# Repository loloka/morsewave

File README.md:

<div align="center">

# 📡 MorseWave

Русский · 🌐 [English](README.en.md)

**Тёмный минималистичный тренажёр азбуки Морзе**
Буквы по отдельности · Метод Коха · Группы символов · Реальные слова · Позывные · XP и достижения

🌐 **[morse.r9old.ru](https://morse.r9old.ru)** — живая версия

</div>

---

## Что это

MorseWave — веб-тренажёр азбуки Морзе, который проведёт от полного нуля до
приёма на слух реальных позывных и подготовки к сдаче радиолюбительского
экзамена (в «Группах» есть режим экзамена по нормативам «Первой категории»).
Без фреймворков на фронтенде и без Bootstrap: чистый JS (Web Audio API) +
собственная тёмная дизайн-система.

Прогресс (XP, уровень, серия дней, выученные символы) хранится локально
в браузере — регистрация не обязательна, тренироваться можно сразу.
Аккаунт — опциональная надстройка, которая даёт три вещи: место в таблице
лидеров на главной (только по явной кнопке «Опубликовать»), синхронизацию
всего прогресса между устройствами (начал на компьютере — продолжил с
телефона) и восстановление доступа по почте. MySQL под капотом хранит
справочные данные (достижения, банк позывных), анонимную статистику
сообщества, аккаунты и серверные копии прогресса.

Интерфейс двуязычный (русский / английский) — переключатель в шапке рядом
с профилем, подробности в разделе «Как это устроено внутри».

## Возможности

| Раздел | Что внутри |
|---|---|
| 📖 **Буквы** | Три подрежима: отправка ключом (тап/пробел, с живым сайдтоном; три набора — «Латиница + цифры», порядок Коха, кириллица), приём на слух (играет символ → нажми на экранной клавиатуре; отдельный набор «Кириллические символы») и **ритм ключа** (сравнивает реальные длительности точки/тире/пауз с идеалом 1:3:1 — скорость свободно регулируется, идеал пересчитывается под неё; 5 точных повторов подряд оттачивают ритм буквы и дают разовый XP; наборы — «Латиница + цифры» и кириллица, без порядка Коха — он там ни при чём) |
| 👾 **Вторжение** (BETA) | Мини-игра-тауэр-дефенс рядом с «Буквами»: пришельцы летят на базу с буквой на слух, символ надо распознать и нажать на самодельной QWERTY-клавиатуре (или на физической клавиатуре компа) до того, как враг долетит — с базы летит лопата. Скорость врага зависит от сложности кода символа, до 5 одновременных целей по ходу волны из 100 попаданий, победная волна даёт бонус XP от остатка HP базы и скорости реакции |
| 🎯 **Метод Коха** | Символы сразу на целевой скорости; новый символ открывается при точности ≥90%; можно вручную установить любое число открытых символов (в обе стороны) |
| 🔢 **Группы символов** | Приём на слух групп по 2–5 символов: буквы / цифры / микс / только выученные / свои, скорость и интервалы Фарнсворта — слайдерами; режим экзамена по нормативам радиолюбительской категории |
| 📝 **Реальные слова** | Приём частых английских слов и радиообменных фраз (`CQ CQ DE R9OGL K`, `UR RST 599 599`): тренирует узнавание слова единым звуковым образом, а не сборку по буквам. Третий таб в «Группах» |
| 💬 **Сокращения** | Q-коды и радиолюбительские сокращения (CQ, QTH, 73…) на слух с вариантами ответа |
| 📡 **Позывные** | Тренировка на реальных по формату позывных (включая российские форматы), банк расширяется скриптом-генератором |
| 🏆 **Достижения** | Ачивки, условия хранятся в БД (`achievements`) — можно добавлять новые без правки кода |
| 🎯 **Задание дня** | Целевое задание под этап игрока (новичку — «изучи буквы», дальше — «прими на слух», знающему алфавит — группы) + бонус +50 XP раз в день |
| 💡 **Сигнальная лампа** | Визуальный аналог звука — можно тренироваться совсем без звука |
| 🏆 **Таблица лидеров** | Топ-10 на главной по опыту и по серии дней + отдельной строкой настоящее место залогиненного пользователя, если он не попал в десятку; отдельная страница со всей таблицей целиком (`leaderboard.php`), публикация — только по явной кнопке «Опубликовать» |
| 👤 **Аккаунт** | Опционально: синхронизация прогресса между устройствами с индикатором «когда синхронизировано», восстановление пароля по почте, самостоятельное удаление аккаунта |
| 💾 **Бэкап прогресса** | Скачать/загрузить прогресс файлом на странице профиля — аккаунт не нужен. Импорт сливает данные «только вверх», поэтому старый файл поверх нового прогресса безопасен |
| ⚠️ **Сброс прогресса** | Кнопка на странице «Достижения» — полный сброс (localStorage и серверной копии) с подтверждением |
| 🌐 **Русский / English** | Переключатель языка в шапке; письма, юридические страницы и API-ошибки тоже переведены |

## Стек

- **PHP 8+** — без фреймворка, простой роутинг по файлам
- **MySQL / MariaDB** — через PDO
- **Vanilla JS** — Web Audio API для звука, без сборки и npm
- **Кастомный CSS** — дизайн-система в `assets/css/style.css`, без Bootstrap
- **Docker** — для локальной разработки (PHP+Apache, MySQL, phpMyAdmin)

## Запуск и деплой

Коротко — локально через Docker:

```bash
git clone <URL_РЕПО> morse-trainer
cd morse-trainer
docker compose up -d --build
```

Сайт на **http://localhost:8080**, phpMyAdmin на **http://localhost:8081**.

Полные инструкции — запуск без Docker, шпаргалка по командам, деплой на VPS,
миграции базы, настройка почты и **администрирование (кто становится админом
и как передать права)** — в **[DEPLOY.md](DEPLOY.md)**.

## Структура проекта

```
morse-trainer/
├── docker-compose.yml       # локальный запуск: PHP+Apache, MySQL, phpMyAdmin
├── docker/                  # Dockerfile + конфиг Apache (AllowOverride для .htaccess)
├── README.md                 # этот файл — обзор проекта на русском (основной, так видят GitHub-посетители по умолчанию)
├── README.en.md               # обзор проекта на английском
├── DEPLOY.md                  # запуск, деплой, миграции, администрирование
├── CLAUDE.md                 # контекст и правила для Claude Code
├── CHANGELOG.md               # история изменений, v2.49+ (свежие записи сверху)
├── CHANGELOG-archive.md       # история изменений, v2.48 и старше
├── lang/
│   ├── ru.php                # словарь строк интерфейса — русский
│   └── en.php                 # словарь строк интерфейса — английский
├── api/                     # JSON-эндпоинты: achievements, callsigns, stats, register,
│                             #   login, logout, me, sync_progress, refresh_published_stats,
│                             #   leaderboard, verify_email, resend_verification, captcha,
│                             #   admin_users, admin_rename_user, admin_delete_user,
│                             #   admin_set_admin, push_progress, pull_progress,
│                             #   delete_progress, delete_account, request_password_reset,
│                             #   reset_password, update_account, unpublish_stats
├── config/
│   ├── database.example.php # шаблон конфига БД (коммитится)
│   ├── database.php         # реальный конфиг БД с кредами (в .gitignore)
│   ├── mail.example.php      # шаблон конфига почты (коммитится)
│   ├── mail.php               # реальный конфиг почты с ключом (в .gitignore)
│   └── .htaccess               # запрет веб-доступа к папке
├── database/
│   ├── schema.sql            # ЕДИНСТВЕННЫЙ источник истины по схеме БД
│   ├── seed_callsigns.php    # генератор пачки позывных
│   └── .htaccess              # запрет веб-доступа к папке
├── includes/                 # header / footer / nav + auth.php, mailer.php, i18n.php,
│                             #   resend_mailer.php, captcha.php, leaderboard_guard.php
├── storage/sessions/         # файлы PHP-сессий (закрыты .htaccess, в git не хранятся)
├── assets/
│   ├── css/style.css         # дизайн-система
│   └── js/                   # morse-data, daily, audio, progress, signal, input, i18n + страницы
├── index.php                 # главная + задание дня
├── leaderboard.php            # вся таблица лидеров целиком
├── learn.php                 # буквы: отправка / приём на слух / ритм ключа
├── koch.php                  # метод Коха
├── groups.php                # группы символов 2–5 (+ реальные слова, сокращения)
├── callsigns.php              # тренировка позывных
├── achievements.php           # достижения + сброс прогресса
├── account.php                 # профиль (вкладки: аккаунт / звук / отображение / бэкап)
├── terms.php · privacy.php     # пользовательское соглашение и политика конфиденциальности
├── admin.php                    # админка: пользователи, переименование, удаление, выдача прав
└── settings.php                # 301-редирект на account.php (настройки переехали в профиль, v2.24)
```

## За что даётся опыт (XP)

Все начисления округляются до целых. Уровень растёт как `1 + √(XP / 80)`
(т.е. 2-й уровень — 80 XP, 3-й — 320 XP, 5-й — 1280 XP и так далее).

| Режим | Сколько | Условия и защита от фарма |
|---|---|---|
| **Буквы → отправка ключом** | **+25 XP** за символ | Один раз за символ — когда впервые набрана серия из 5 верных повторов подряд. Повторные серии по выученному символу XP не дают. Ставка одинаковая для латиницы и кириллицы — без надбавки за сложность (осознанное упрощение, v2.51.1). |
| **Буквы → приём на слух** | **+1 XP** за верный ответ | Спам верной плиткой в паузе между раундами заблокирован. Ставка одинаковая для латиницы и кириллицы (в v2.51.1 кириллица недолго давала +2, но это путало — одинаково выглядящие латинская и кириллическая «M» получали разный XP; откачено в v2.51.7). |
| **Буквы → ритм ключа** | **+25 XP** разово за букву | Та же анти-фарм схема, что и у отправки ключом: XP не капает за отдельные попытки, а выдаётся один раз, когда набрано 5 точных повторов подряд (буква верная И точность ритма ≥ 80% от идеала 1:3:1). Любая осечка обнуляет серию; повторная тренировка уже отточенной буквы — без XP. |
| **Вторжение** (BETA) | `(База 1 XP) × 2 × (Плотность волны / 3)` (как в Кохе), + бонус `×2` за добивание Босса. Бонус победы волны (10–130 XP). | Награда растет соразмерно плотности волны (количеству пришельцев на экране), используя балансную формулу из Метода Коха/Групп, чтобы предотвратить фарм опыта. Боссы (группы символов) при добивании дают дополнительный опыт, равный их длине ×2. Бонус победы начисляется только за полностью пройденную волну (100 попаданий). |
| **Метод Коха** | `2 × (символов_открыто / 15, но не более 1 и не менее 0.15) × (длина_группы / 3)` XP за каждый верно принятый символ | Чем больше открыто символов и длиннее группы — тем выше ставка (максимум 2 XP/символ при полном наборе). На старте с 2 символами ставка минимальная — фармить лёгкие сессии невыгодно. |
| **Метод Коха — бонус** | **+10/+20/+30 XP** (равен числу групп в сессии) | Только если сессия завершена целиком с точностью ≥ 90 %. Ачивки за метод считаются по честно заработанному уровню (`kochLevelEarned`) — протащить бегунок до конца и получить ачивку нельзя. |
| **Группы символов** | `2 × √(размер_набора / 26, но не более 1 и не менее 0.15) × (длина_группы / 3)` XP за каждый верно принятый символ | Ставка зависит от размера выбранного набора и длины групп. Начисляется сразу за каждую отвеченную группу. |
| **Группы — повтор ошибок** | Опыт **x3** от базового + бонус **5 XP** за безошибочную группу | Генерируются новые случайные группы с замешиванием символов, в которых была ошибка (если перепутал две буквы — в группу попадут обе). Бонус работает как **анти-абуз**: начисляется только если точность в оригинальной сессии была ≥ 60%. Если меньше (умышленный проклик пустых ответов) — XP за ошибки не начисляется (0 XP). |
| **Группы — экзамен** | ставка сессии × верные символы | Только если экзамен доигран до конца — досрочная остановка обнуляет XP экзамена (в общие счётчики группы всё равно идут). |
| **Реальные слова** | **1.2 XP** за символ (слова) / **1.5 XP** (фразы) | Ставка ниже, чем в группах: связный текст предсказуем, недослышанную букву можно восстановить по смыслу. Если слово принято хуже чем на 60 % — XP за него не начисляется вовсе (иначе банк слов фармился бы вслепую). Пробелы во фразах в счёт не идут. |
| **Сокращения (Q-коды)** | **+5 XP** за верный ответ | — |
| **Позывные** | **+20 XP** за верно принятый позывной | Начисляется сразу, не дожидаясь конца сессии. |
| **Задание дня** | **+50 XP** бонусом | Один раз в день. Задание целевое под этап игрока (см. `daily.js`): новичку — «изучи 3 новые буквы», осваивающемуся — «прими 20 символов на слух», знающему алфавит — приём групп. Для группового задания параметры сессии должны совпадать с заданием **и точность быть не ниже 50 %** (прокликать пустые ответы не выйдет, фикс v2.26). |
| **Бонус за скорость (только в задании дня)** | множитель XP `speedXpFactor(wpm)`: ≤12 wpm → ×1.0, выше — +4 %/wpm, потолок ×1.6 (≈27 wpm) | Применяется **только** к групповому заданию дня, где скорость навязана. В обычных сессиях, «Реальных словах» и Кохе не действует — там скорость выбирает сам человек. Смысл: не заставлять новичка гнаться за 24 wpm ради тех же 50 XP, но честно доплачивать за высокий темп. Фарма нет — XP по-прежнему только за верный символ, а быстро принять сложнее. |

### Почему формулы в Кохе и Группах разные

Выглядит как недосмотр, но это осознанное решение (v2.33) — не сводите их
к одной.

В **Группах** набор символов выбирает сам человек, поэтому маленький набор
обязан давать пропорционально меньше XP. Прежний делитель 15 упирался в
потолок слишком рано: свой набор из 15 самых лёгких знаков давал ровно ту
же ставку, что полный алфавит из 36, — это была работающая лазейка.
Делитель 26 (полный латинский алфавит) её закрывает, а корень вместо
линейной пропорции нужен, чтобы честные промежуточные наборы вроде «Цифры»
(10 знаков) не штрафовались слишком жёстко. Числа подобраны так, что оба
основных пресета — «Буквы» (26) и «Буквы + цифры» (36) — дают прежние
2.0 XP/символ: баланс существующих режимов не поехал.

В **Кохе** набор задан уровнем, а не выбором человека. Пофармить маленьким
набором там нельзя в принципе: для этого пришлось бы сидеть на низком
уровне, который и так даёт минимальную ставку. Поэтому формула осталась
старой — ужесточение не закрыло бы ни одной лазейки, зато срезало бы
мотивацию на средних уровнях метода.

Серия дней (🔥 streak) засчитывается только за реальную завершённую
тренировку (сессия Коха/групп/позывных или задание дня) — просто зайти на
сайт недостаточно.

## Как это устроено внутри

- **`assets/js/audio.js`** — `MorseAudio` проигрывает точки/тире через
  осциллятор Web Audio API, поддерживает интервалы Фарнсворта (символы на
  одной скорости, паузы — на другой, более медленной). `onSymbol` колбэк
  отдаёт `durationMs` — используется для точной синхронизации визуализации.
- **`assets/js/input.js`** — `TelegraphKey` превращает удержание клавиши
  (тап по экрану или пробел) в точки/тире по длительности нажатия
  относительно текущего `wpm`, плюс живой сайдтон (реальный звук) во время
  удержания. Пороги: `< 2×unit` → точка, иначе тире; пауза `2.5×unit` —
  граница буквы, ещё `+4×unit` — граница слова.
- **`assets/js/daily.js`** — `DailyChallenge`: единый источник «задания дня»
  для главной и режимов-исполнителей, задание считается из пары
  «дата + этап игрока».
- **`assets/js/signal.js`** — `SignalLine` (осциллограф из точек/тире) и
  `MorseLamp` (визуальная лампа) — сквозные визуальные элементы, синхронно
  отражающие и звук, и ввод на всех страницах тренировки.
- **`assets/js/progress.js`** — весь прогресс пользователя в одном ключе
  `localStorage` (`morsewave_progress_v1`): XP, уровень, серия дней,
  выученные символы, уровень Коха, статистика, разблокированные
  достижения. `Progress.resetAll()` — полный сброс.
- **Синхронизация и её индикатор.** `Progress.pushNow()` шлёт весь
  Progress-объект в `api/push_progress.php` и при ответе `ok: true`
  запоминает момент в отдельном ключе `morsewave_last_sync` + шлёт событие
  `progress:synced`; `account.js` рисует по нему строку «☁ Синхронизировано:
  5 минут назад». Метка ставится **только** при реальном успехе.
- **Бэкап файлом** — `Progress.exportBackup()` / `Progress.importBackup()`.
  Импорт намеренно идёт через тот же `mergeFromServer()`, что и слияние при
  логине: «только вверх» (max по числам, union по множествам). Поэтому
  загрузить старый файл поверх свежего прогресса безопасно.
- **Достижения** определяются в MySQL (`achievements`, поле `condition_type`
  + `condition_value`), а проверка условий против статистики происходит на
  клиенте в `Progress.checkAchievements()` — сопоставление типов см. в
  `progress.js` (`statValue()`).
- **Защита лидерборда** (`includes/leaderboard_guard.php`) — перед публикацией
  в `user_stats` значения обрезаются по правдоподобному потолку (привязан к
  возрасту аккаунта), отсекая грубую накрутку. Реальный прогресс не меняется —
  режется только публичная строка (подробности в CHANGELOG, v2.40).
- **Интернационализация** (`includes/i18n.php`, `lang/ru.php`, `lang/en.php`,
  `assets/js/i18n.js`) — язык выбирается по `?lang=` → cookie `mw_lang` →
  `Accept-Language` браузера → по умолчанию русский. Хелпер `t('ключ')`
  доступен и в PHP-шаблонах, и (как глобальная функция `t()`) в JS через
  `window.MW_I18N`, который `includes/header.php` кладёт в `<head>`.
  Фолбэк при отсутствующем переводе: текущий язык → русский → сам ключ.
  Слоговые мнемоники букв (`MORSE_MNEMONICS` и `CYRILLIC_MNEMONICS` в
  `morse-data.js`) — фонетическая подсказка, завязанная на русское звучание,
  поэтому в английском интерфейсе она осознанно отключена, а не переведена
  дословно.
- **Кириллическая азбука Морзе** (`learn.php`, v2.51) — отдельная таблица
  на 33 кода (`CYRILLIC_CODE`/`CYRILLIC_TO_CHAR` в `morse-data.js`, в обучающем
  наборе 31 буква — `Ъ` и `Ё` исключены из тренировок, чтобы не путать с `Е` и не
  загромождать процесс редкими знаками), намеренно *не* смешанная с латинской
  `MORSE_CODE`/`MORSE_TO_CHAR`: часть кириллических букв совпадает по коду с
  «похожей по звучанию» латинской (так исторически устроена сама азбука), поэтому
  общий реверс-словарь сделал бы декодирование ключом непредсказуемым.
  `TelegraphKey` (`input.js`) принимает таблицу декодирования параметром/через
  `setTable()`, а не жёстко зашитым глобалом. Прогресс по кириллице хранится с
  префиксом `RU_` (`learnedLetters`) — латинская `A` и кириллическая `А` никогда
  не пересекаются, а ачивка «Полный алфавит» считается строго по латинице+цифрам
  (`progress.js`), несмотря на то что кириллические записи лежат в том же массиве.

## История изменений

Актуальная история (v2.49 и новее) — в [CHANGELOG.md](CHANGELOG.md), свежие
записи сверху. Более ранние версии, вплоть до самой первой, —
в [CHANGELOG-archive.md](CHANGELOG-archive.md).

## Известные ограничения / открытые вопросы

- Аккаунты — опциональная надстройка над localStorage (не обязательны для
  тренировки). Клиент остаётся источником истины по XP, поэтому абсолютной
  защиты от накрутки нет; публичный лидерборд прикрыт серверным санитарным
  потолком (`leaderboard_guard.php`, v2.40) — он отсекает грубые значения,
  но это «замок от честных людей», а не пуленепробиваемая защита. Один и тот
  же прогресс из одного браузера технически можно опубликовать от нескольких
  аккаунтов — барьером служит email-подтверждение + мягкое предупреждение
  при повторной публикации.
- Письма шлются через **Resend API** (см. [DEPLOY.md](DEPLOY.md)) — на
  shared-хостинге SMTP оказался ненадёжен (нет DKIM, PTR общего IP не
  указывает на домен, Gmail тихо режет письма).
- Капча на азбуке Морзе (`includes/captcha.php`) — базовая защита от
  примитивных скриптов, не от целенаправленного обхода.
- `TelegraphKey` калибрует точку/тире относительно выбранного `wpm`, а не
  адаптируется к реальному темпу пользователя.
- Кириллица есть только в «Буквах» (отправка + приём на слух) — «Метод Коха»
  и «Группы символов» остаются латинскими. Это осознанно, не недосмотр:
  у Коха фиксированный классический порядок символов, который по
  определению латинский, а Группы/режим экзамена ориентированы на программу
  радиолюбительского экзамена (латиница+цифры) — кириллический набор там
  просто не на что было бы натянуть.

## Roadmap / идеи для развития

Порядок примерно = приоритет (подробности и нюансы — в [CLAUDE.md](CLAUDE.md)):

- [ ] **Свой адаптивный декодер приёма на слух** — подстраивается под
  реальную скорость передачи по таймстемпам, а не под выбранный wpm
- [ ] **Адаптивная калибровка ключа** под реальный темп пользователя
- [ ] _(дальний прицел)_ Нативное Android-приложение (не PWA)
- [ ] _(исследование)_ Подключение реального телеграфного ключа (адаптер на
  Arduino / Web Serial / микрофонный вход)

Уже сделано: восстановление пароля по почте, экспорт/импорт прогресса файлом,
целевые задания дня, самостоятельное удаление аккаунта, защита лидерборда,
двуязычный интерфейс (русский/английский), кириллическая азбука Морзе в
«Буквах» (v2.51), полная таблица лидеров + своё место на главной (v2.52),
оценка ритма ключа в «Буквах» (v2.53), мини-игра «Вторжение» — тауэр-дефенс
на азбуку Морзе (v2.54, статус BETA), достижения за волны вторжения и за
отточенный ритм ключа (v2.55–v2.56).

## Смежный проект

Освоил приём отдельных знаков и позывных — дальше по маршруту (см. «Путь
новичка» на главной) идёт **[Morse Walker](https://morse.r9o.ru)**:
симулятор радиосвязи с pile-up, режимы контестов и POTA, генератор
российских позывных. Это отдельный проект, не часть MorseWave — исходный
автор [W6NYC](https://github.com/sc0tfree/morsewalker), доработка и
русификация — тоже R9OGL: [github.com/loloka/morsewalker](https://github.com/loloka/morsewalker).

## Лицензия

MIT — делай с этим что хочешь, см. [LICENSE](LICENSE).

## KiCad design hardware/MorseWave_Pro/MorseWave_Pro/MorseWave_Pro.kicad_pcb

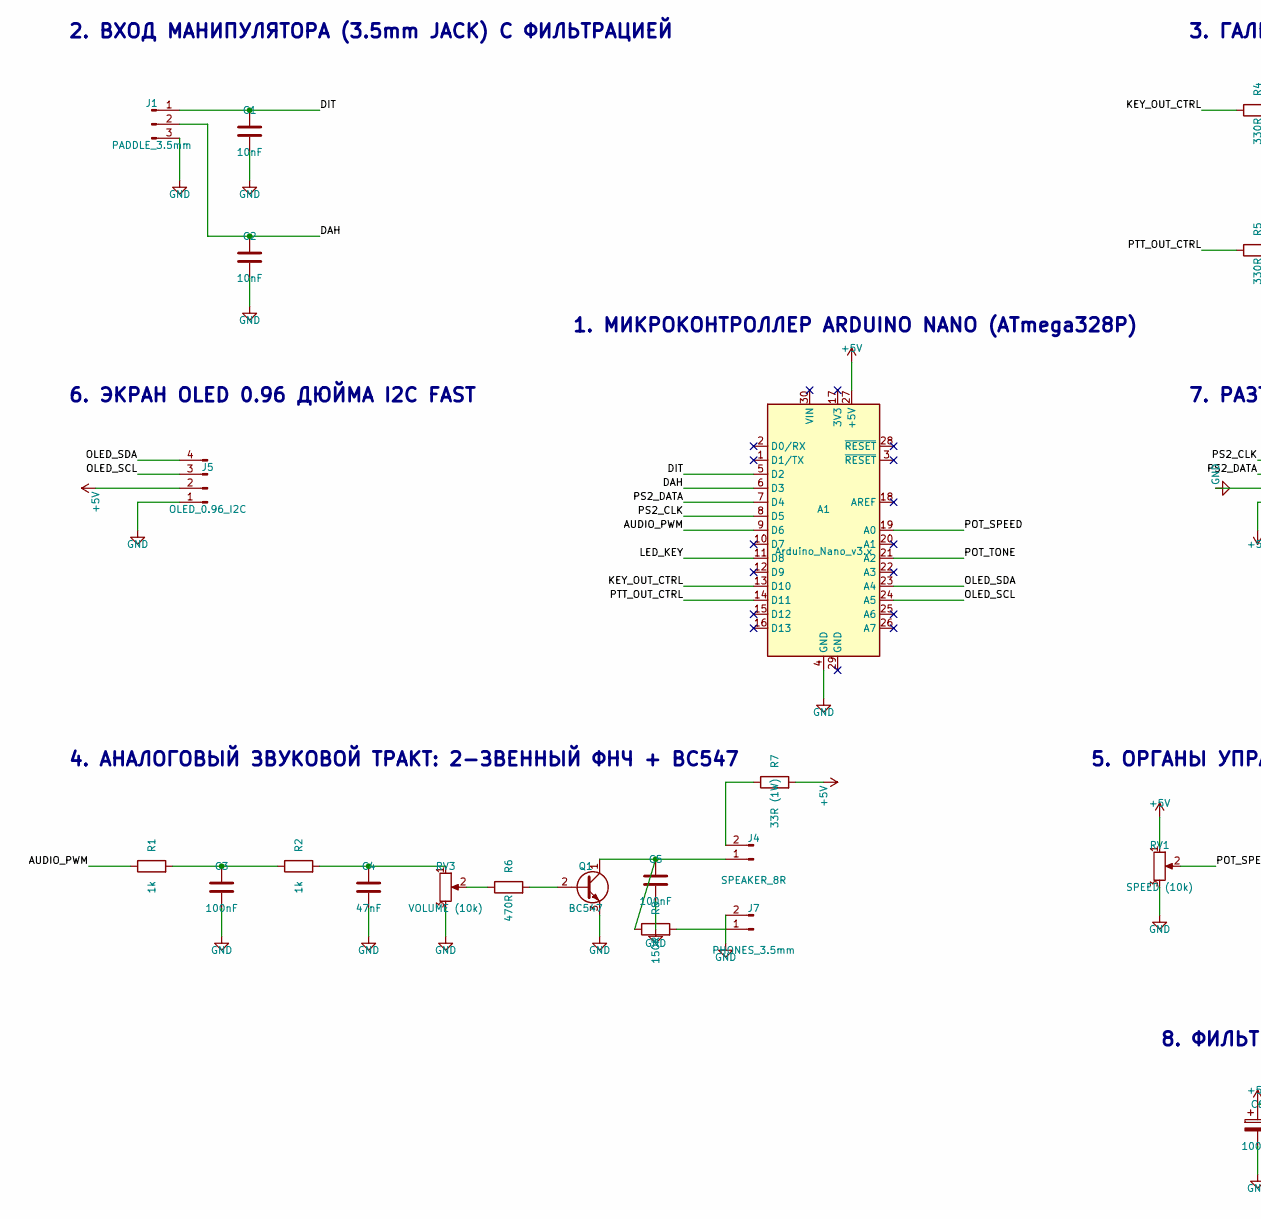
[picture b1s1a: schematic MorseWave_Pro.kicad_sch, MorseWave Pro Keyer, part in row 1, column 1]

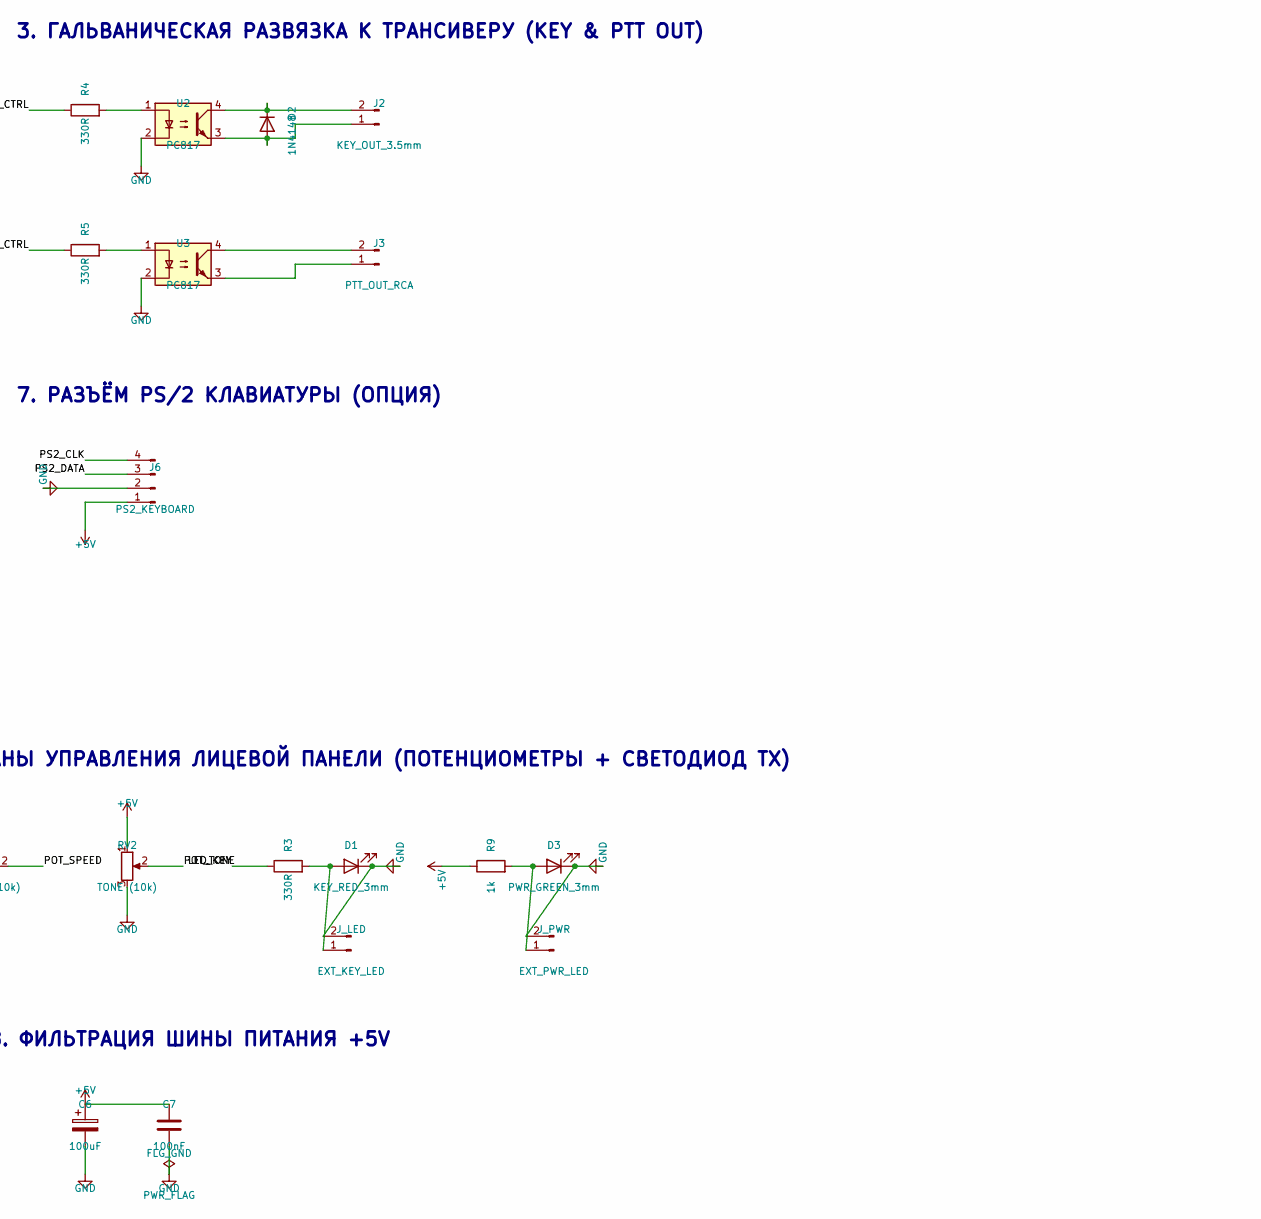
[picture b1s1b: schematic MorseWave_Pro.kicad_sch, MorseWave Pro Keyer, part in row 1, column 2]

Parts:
A1: Arduino_Nano_v3.x; Arduino_Nano
C1, C2: 10nF; C_Disc_D5.0mm_W2.5mm_P5.00mm
C3, C5, C7: 100nF; C_Disc_D5.0mm_W2.5mm_P5.00mm
C4: 47nF; C_Disc_D5.0mm_W2.5mm_P5.00mm
C6: 100uF; CP_Radial_D6.3mm_P2.50mm
D1: KEY_RED_3mm; LED_D3.0mm
D2: 1N4148; D_DO-35_SOD27_P7.62mm_Horizontal
D3: PWR_GREEN_3mm; LED_D3.0mm
FLG_GND: PWR_FLAG
J1: PADDLE_3.5mm; PinHeader_1x03_P2.54mm_Vertical
J2: KEY_OUT_3.5mm; PinHeader_1x02_P2.54mm_Vertical
J3: PTT_OUT_RCA; PinHeader_1x02_P2.54mm_Vertical
J4: SPEAKER_8R; PinHeader_1x02_P2.54mm_Vertical
J5: OLED_0.96_I2C; PinSocket_1x04_P2.54mm_Vertical
J6: PS2_KEYBOARD; PinHeader_1x04_P2.54mm_Vertical
J7: PHONES_3.5mm; PinHeader_1x02_P2.54mm_Vertical
J_LED: EXT_KEY_LED; PinHeader_1x02_P2.54mm_Vertical
J_PWR: EXT_PWR_LED; PinHeader_1x02_P2.54mm_Vertical
Q1: BC547; TO-92_Inline
R1, R2, R9: 1k; R_Axial_DIN0207_L6.3mm_D2.5mm_P7.62mm_Horizontal
R3, R4, R5: 330R; R_Axial_DIN0207_L6.3mm_D2.5mm_P7.62mm_Horizontal
R6: 470R; R_Axial_DIN0207_L6.3mm_D2.5mm_P7.62mm_Horizontal
R7: 33R (1W); R_Axial_DIN0411_L9.9mm_D3.6mm_P12.70mm_Horizontal
R8: 150R; R_Axial_DIN0207_L6.3mm_D2.5mm_P7.62mm_Horizontal
RV1: SPEED (10k); PinHeader_1x03_P2.54mm_Vertical
RV2: TONE (10k); PinHeader_1x03_P2.54mm_Vertical
RV3: VOLUME (10k); PinHeader_1x03_P2.54mm_Vertical
U2, U3: PC817; DIP-4_W7.62mm

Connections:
+5V: A1.27 (+5V), C6.1, C7.1, J5.2, J6.1, R7.2, R9.1, RV1.1, RV2.1
/AUDIO_PWM: A1.9 (D6), R1.1
/DAH: A1.6 (D3), C2.1, J1.2
/DIT: A1.5 (D2), C1.1, J1.1
/KEY_OUT_CTRL: A1.13 (D10), R4.1
/LED_KEY: A1.11 (D8), R3.1
/OLED_SCL: A1.24 (A5), J5.3
/OLED_SDA: A1.23 (A4), J5.4
/POT_SPEED: A1.19 (A0), RV1.2
/POT_TONE: A1.21 (A2), RV2.2
/PS2_CLK: A1.8 (D5), J6.4
/PS2_DATA: A1.7 (D4), J6.3
/PTT_OUT_CTRL: A1.14 (D11), R5.1
GND: A1.4 (GND), C1.2, C2.2, C3.2, C4.2, C5.2, C6.2, C7.2, D1.1 (K), D3.1 (K), FLG_GND.1, J1.3, J5.1, J6.2, J7.2, J_LED.2, J_PWR.2, Q1.3 (E), RV1.3, RV2.3, RV3.3, U2.2, U3.2
unnamed: C3.1, R1.2, R2.1
unnamed: C4.1, R2.2, RV3.1
unnamed: D1.2 (A), J_LED.1, R3.2
unnamed: D2.2 (A), J2.1, U2.3
unnamed: D2.1 (K), J2.2, U2.4
unnamed: D3.2 (A), J_PWR.1, R9.2
unnamed: J3.1, U3.3
unnamed: J3.2, U3.4
unnamed: C5.1, J4.1, Q1.1 (C), R8.1
unnamed: J4.2, R7.1
unnamed: J7.1, R8.2
unnamed: Q1.2 (B), R6.2
unnamed: R4.2, U2.1
unnamed: R5.2, U3.1
unnamed: R6.1, RV3.2

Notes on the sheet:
1. МИКРОКОНТРОЛЛЕР ARDUINO NANO (ATmega328P)
2. ВХОД МАНИПУЛЯТОРА (3.5mm JACK) С ФИЛЬТРАЦИЕЙ
3. ГАЛЬВАНИЧЕСКАЯ РАЗВЯЗКА К ТРАНСИВЕРУ (KEY & PTT OUT)
4. АНАЛОГОВЫЙ ЗВУКОВОЙ ТРАКТ: 2-ЗВЕННЫЙ ФНЧ + BC547
5. ОРГАНЫ УПРАВЛЕНИЯ ЛИЦЕВОЙ ПАНЕЛИ (ПОТЕНЦИОМЕТРЫ + СВЕТОДИОД TX)
6. ЭКРАН OLED 0.96 ДЮЙМА I2C FAST
7. РАЗЪЁМ PS/2 КЛАВИАТУРЫ (ОПЦИЯ)
8. ФИЛЬТРАЦИЯ ШИНЫ ПИТАНИЯ +5V

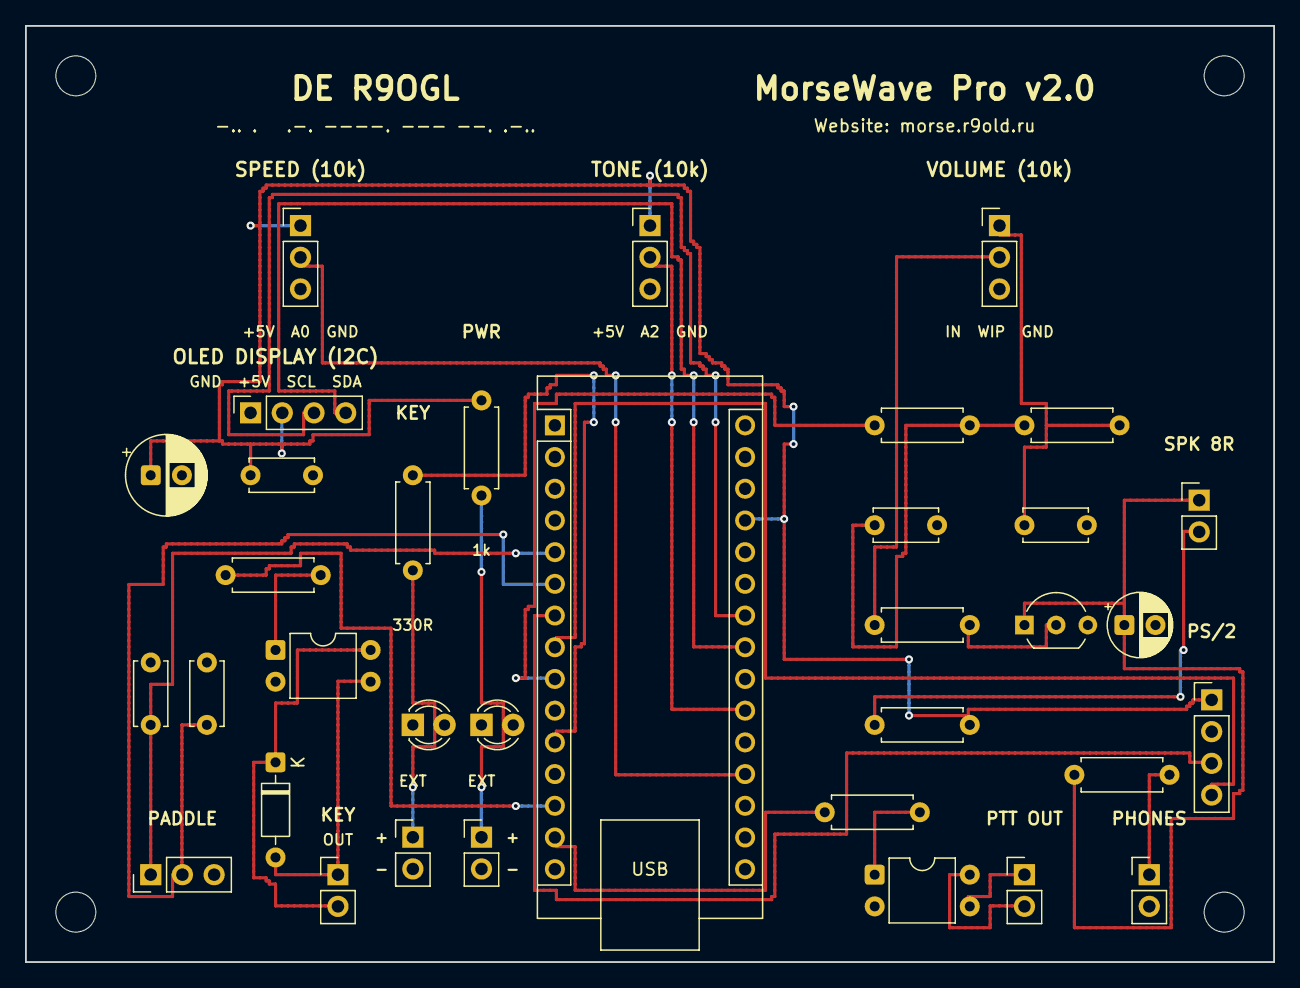
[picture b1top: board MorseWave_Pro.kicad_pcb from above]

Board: 2 copper layers, 100.0 x 75.0 mm, 39 parts (0 on the bottom side), 29 nets.

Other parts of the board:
H1, H2, H3, H4: MountingHole_M3; MountingHole_3.2mm_M3

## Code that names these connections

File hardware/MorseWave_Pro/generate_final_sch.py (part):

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s.no_connect(*s.pin_pos("A1", 2))
s.no_connect(*s.pin_pos("A1", 1))

# D2 (DIT) - Nano pin 5
p_d2 = s.pin_pos("A1", 5)
s.wr(p_d2[0], p_d2[1], p_d2[0] - 12.70, p_d2[1])
s.lbl("DIT", p_d2[0] - 12.70, p_d2[1], 0, "right bottom")

# D3 (DAH) - Nano pin 6
p_d3 = s.pin_pos("A1", 6)
s.wr(p_d3[0], p_d3[1], p_d3[0] - 12.70, p_d3[1])
s.lbl("DAH", p_d3[0] - 12.70, p_d3[1], 0, "right bottom")

# D4 (PS2_DATA) - Nano pin 7
p_d4 = s.pin_pos("A1", 7)
s.wr(p_d4[0], p_d4[1], p_d4[0] - 12.70, p_d4[1])
s.lbl("PS2_DATA", p_d4[0] - 12.70, p_d4[1], 0, "right bottom")

# D5 (PS2_CLK) - Nano pin 8
p_d5 = s.pin_pos("A1", 8)
s.wr(p_d5[0], p_d5[1], p_d5[0] - 12.70, p_d5[1])
s.lbl("PS2_CLK", p_d5[0] - 12.70, p_d5[1], 0, "right bottom")

# D6 (AUDIO_PWM) - Nano pin 9 (matches firmware PIN_AUDIO = 6)
p_d6 = s.pin_pos("A1", 9)
s.wr(p_d6[0], p_d6[1], p_d6[0] - 12.70, p_d6[1])
s.lbl("AUDIO_PWM", p_d6[0] - 12.70, p_d6[1], 0, "right bottom")
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# D7 (no connect) - Nano pin 10
s.no_connect(*s.pin_pos("A1", 10))

# D8 (LED_KEY) - Nano pin 11 (matches firmware PIN_LED_KEY = 8, Green LED)
p_d8 = s.pin_pos("A1", 11)
s.wr(p_d8[0], p_d8[1], p_d8[0] - 12.70, p_d8[1])
s.lbl("LED_KEY", p_d8[0] - 12.70, p_d8[1], 0, "right bottom")
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# D9 (no connect) - Nano pin 12
s.no_connect(*s.pin_pos("A1", 12))

# D10 (KEY_OUT_CTRL) - Nano pin 13
p_d10 = s.pin_pos("A1", 13)
s.wr(p_d10[0], p_d10[1], p_d10[0] - 12.70, p_d10[1])
s.lbl("KEY_OUT_CTRL", p_d10[0] - 12.70, p_d10[1], 0, "right bottom")

# D11 (PTT_OUT_CTRL) - Nano pin 14
p_d11 = s.pin_pos("A1", 14)
s.wr(p_d11[0], p_d11[1], p_d11[0] - 12.70, p_d11[1])
s.lbl("PTT_OUT_CTRL", p_d11[0] - 12.70, p_d11[1], 0, "right bottom")
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s.no_connect(*s.pin_pos("A1", 3))
s.no_connect(*s.pin_pos("A1", 18))

# A0 (POT_SPEED) - Nano pin 19 (matches firmware PIN_POT_WPM = A0)
p_a0 = s.pin_pos("A1", 19)
s.wr(p_a0[0], p_a0[1], p_a0[0] + 12.70, p_a0[1])
s.lbl("POT_SPEED", p_a0[0] + 12.70, p_a0[1], 0, "left bottom")
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# A1 (no connect) - Nano pin 20
s.no_connect(*s.pin_pos("A1", 20))

# A2 (POT_TONE) - Nano pin 21 (matches firmware PIN_POT_PITCH = A2)
p_a2 = s.pin_pos("A1", 21)
s.wr(p_a2[0], p_a2[1], p_a2[0] + 12.70, p_a2[1])
s.lbl("POT_TONE", p_a2[0] + 12.70, p_a2[1], 0, "left bottom")
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J1_Y = 55.88
s.sym("J1", "PADDLE_3.5mm", "Connector_PinHeader_2.54mm:PinHeader_1x03_P2.54mm_Vertical", "Connector", "Conn_01x03_Pin", J1_X, J1_Y, 0)

p_j1_1 = s.pin_pos("J1", 1)  # DIT
p_j1_2 = s.pin_pos("J1", 2)  # DAH
p_j1_3 = s.pin_pos("J1", 3)  # GND

# DIT line
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s.sym("J5", "OLED_0.96_I2C", "Connector_PinSocket_2.54mm:PinSocket_1x04_P2.54mm_Vertical", "Connector", "Conn_01x04_Pin", 55.88, 121.92, 180)
p_j5_1 = s.pin_pos("J5", 1)  # GND
p_j5_2 = s.pin_pos("J5", 2)  # +5V
p_j5_3 = s.pin_pos("J5", 3)  # OLED_SCL
p_j5_4 = s.pin_pos("J5", 4)  # OLED_SDA

# Pin 1: GND (bottom pin, Y=124.46) - route left and DOWN
s.wr(p_j5_1[0], p_j5_1[1], p_j5_1[0] - 7.62, p_j5_1[1])
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s.wr(p_j5_2[0], p_j5_2[1], p_j5_2[0] - 15.24, p_j5_2[1])
s.pwr("+5V", p_j5_2[0] - 15.24, p_j5_2[1], 90)

# Pin 3: OLED_SCL (Y=119.38)
s.wr(p_j5_3[0], p_j5_3[1], p_j5_3[0] - 7.62, p_j5_3[1])
s.lbl("OLED_SCL", p_j5_3[0] - 7.62, p_j5_3[1], 0, "right bottom")

# Pin 4: OLED_SDA (top pin, Y=116.84)
s.wr(p_j5_4[0], p_j5_4[1], p_j5_4[0] - 7.62, p_j5_4[1])
s.lbl("OLED_SDA", p_j5_4[0] - 7.62, p_j5_4[1], 0, "right bottom")

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s.sym("J6", "PS2_KEYBOARD", "Connector_PinHeader_2.54mm:PinHeader_1x04_P2.54mm_Vertical", "Connector", "Conn_01x04_Pin", 259.08, 121.92, 180)
p_j6_1 = s.pin_pos("J6", 1)  # +5V (bottom pin, Y=124.46)
p_j6_2 = s.pin_pos("J6", 2)  # GND (Y=121.92)
p_j6_3 = s.pin_pos("J6", 3)  # PS2_DATA (Y=119.38)
p_j6_4 = s.pin_pos("J6", 4)  # PS2_CLK (top pin, Y=116.84)

# Pin 1: +5V (bottom pin) - route left and DOWN
s.wr(p_j6_1[0], p_j6_1[1], p_j6_1[0] - 7.62, p_j6_1[1])
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s.wr(p_j6_2[0], p_j6_2[1], p_j6_2[0] - 15.24, p_j6_2[1])
s.pwr("GND", p_j6_2[0] - 15.24, p_j6_2[1], 90)

# Pin 3: PS2_DATA
s.wr(p_j6_3[0], p_j6_3[1], p_j6_3[0] - 7.62, p_j6_3[1])
s.lbl("PS2_DATA", p_j6_3[0] - 7.62, p_j6_3[1], 0, "right bottom")

# Pin 4: PS2_CLK
s.wr(p_j6_4[0], p_j6_4[1], p_j6_4[0] - 7.62, p_j6_4[1])
s.lbl("PS2_CLK", p_j6_4[0] - 7.62, p_j6_4[1], 0, "right bottom")

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

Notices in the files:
README.md:
License: MIT
